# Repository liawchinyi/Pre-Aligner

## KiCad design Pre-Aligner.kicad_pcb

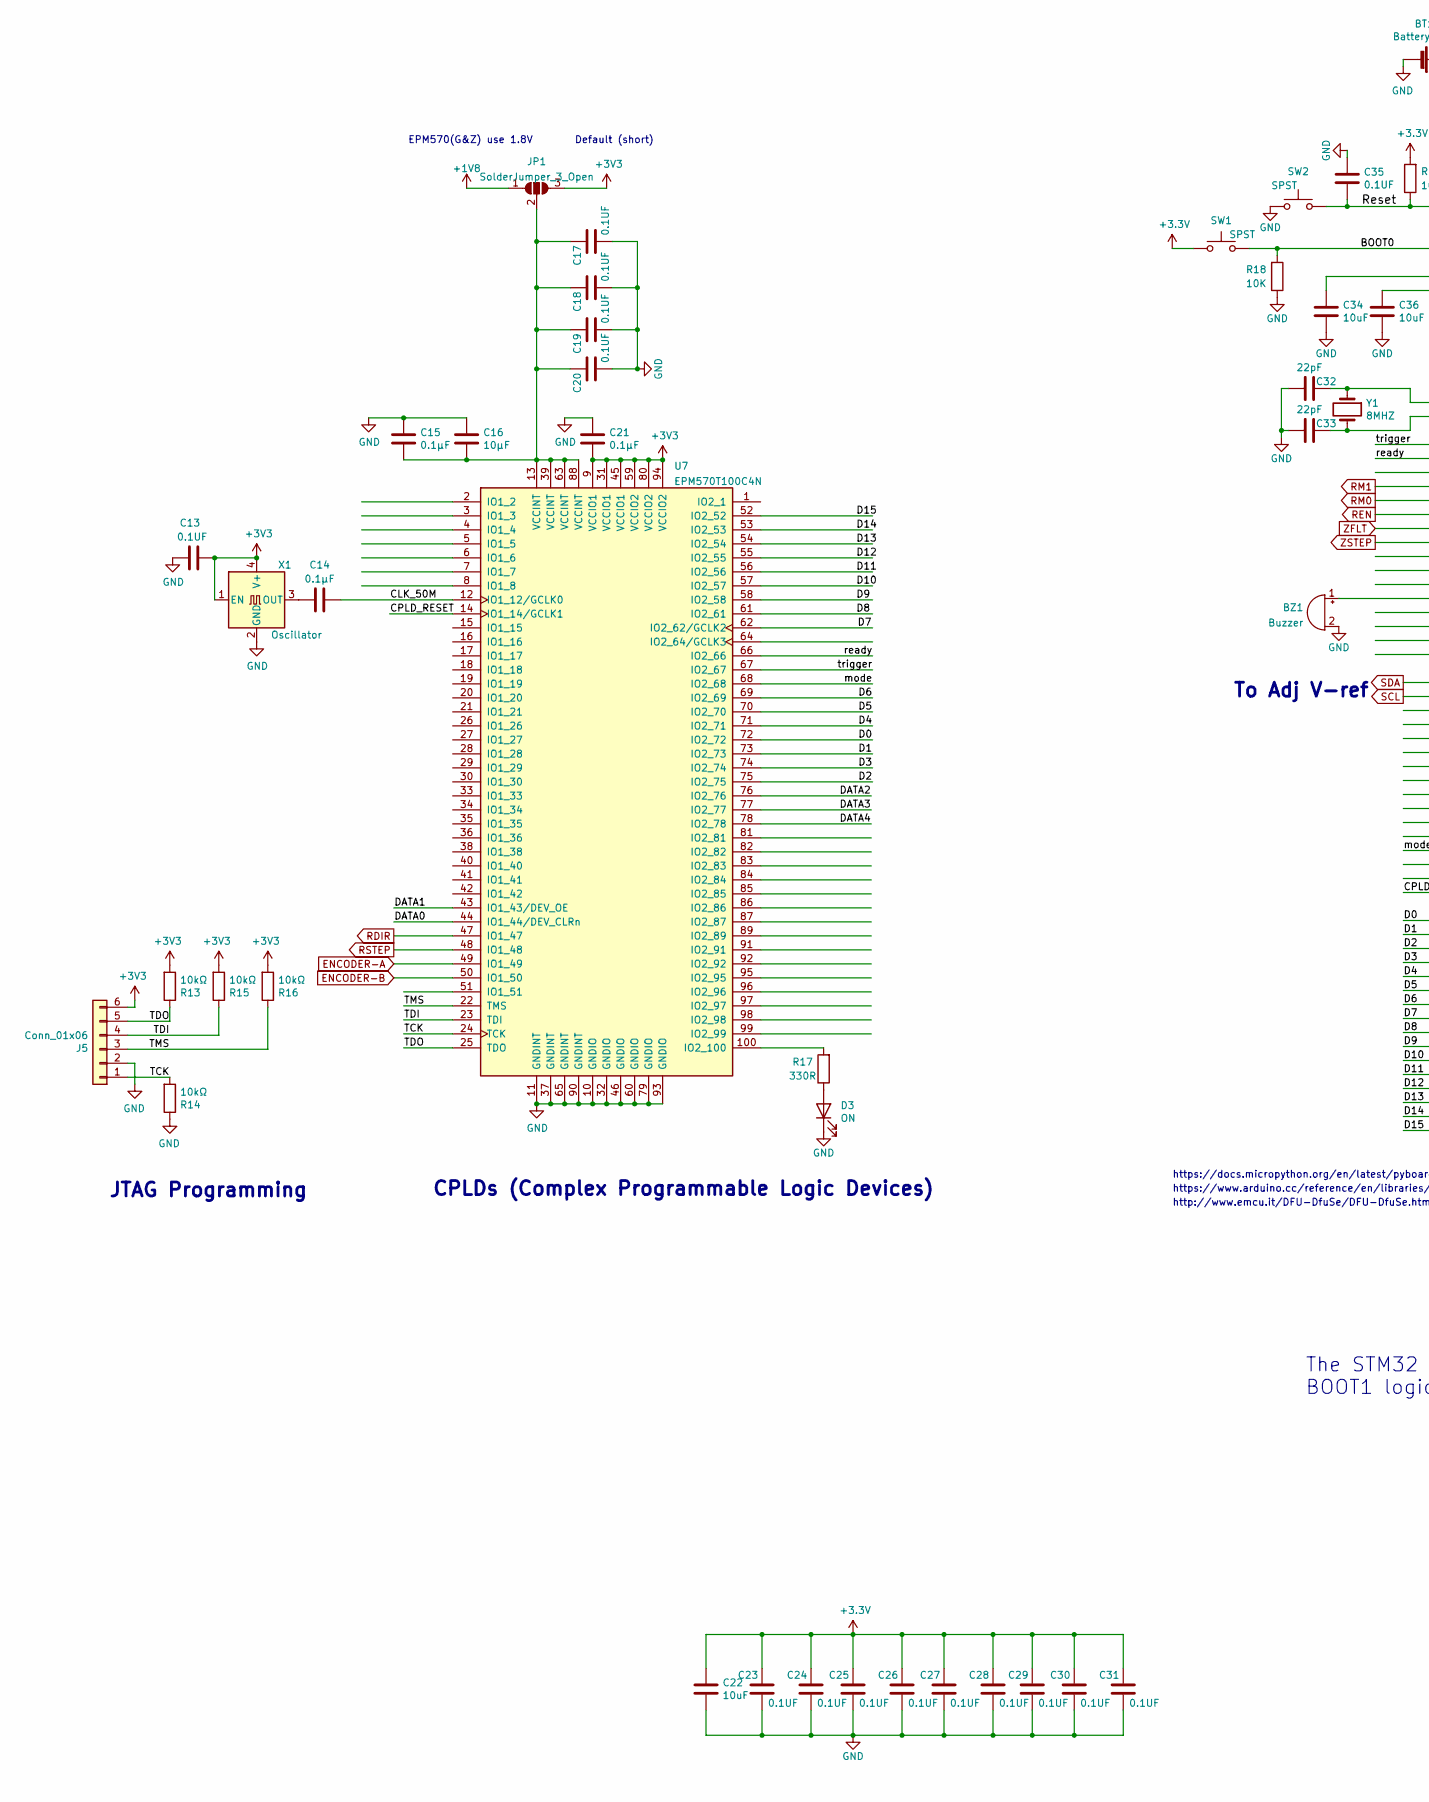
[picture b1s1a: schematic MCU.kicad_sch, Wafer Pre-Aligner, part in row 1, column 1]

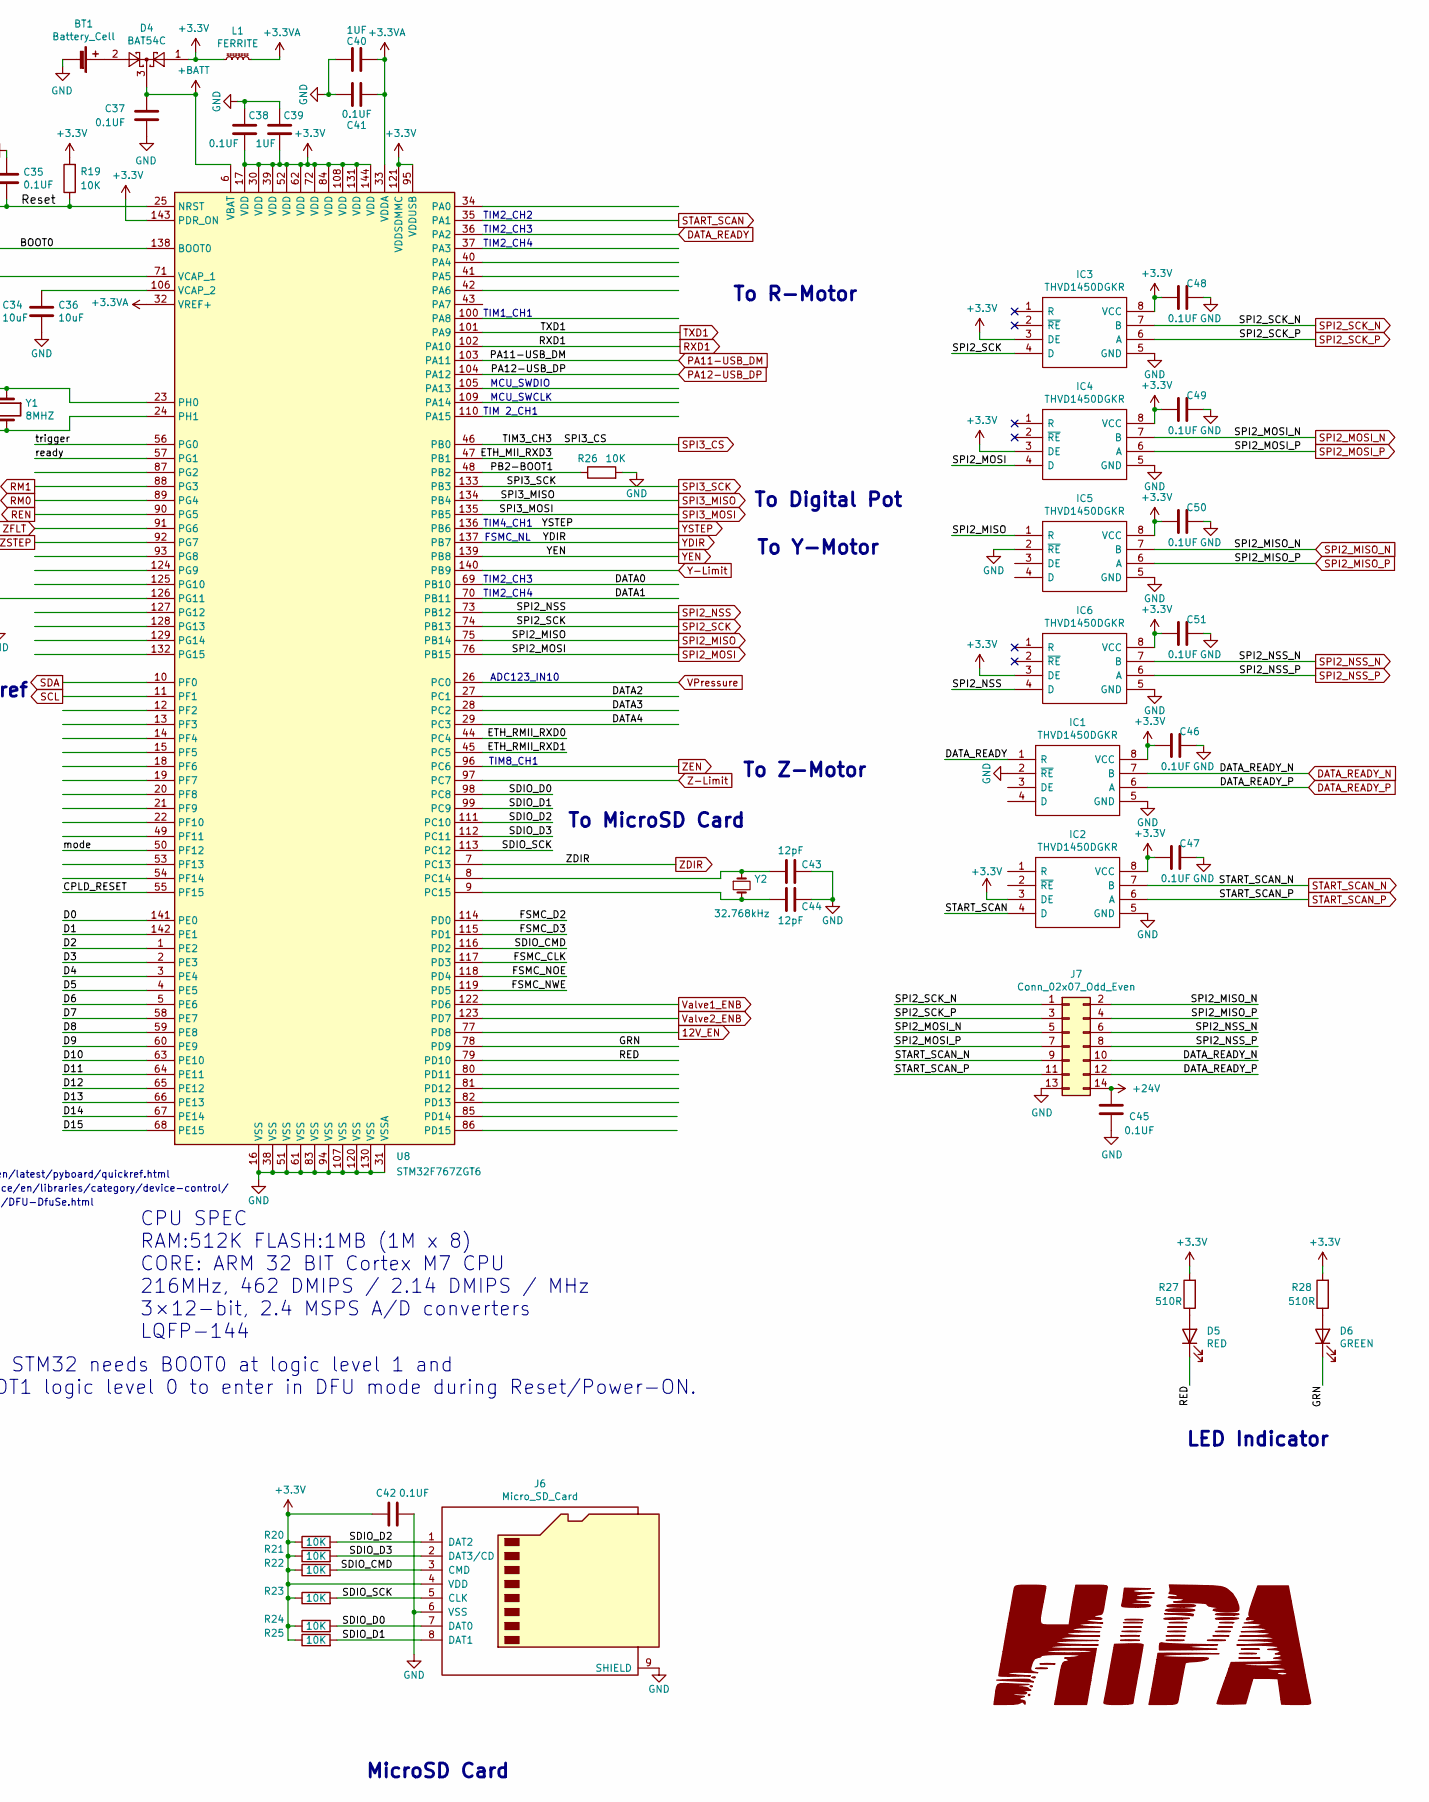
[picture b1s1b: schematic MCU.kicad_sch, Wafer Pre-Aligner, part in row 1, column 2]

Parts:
BT1: Battery_Cell; S8411-45R; Manufacturer_Part_Number S8411-45R
BZ1: Buzzer; MagneticBuzzer_PUI_AT-0927-TT-6-R; Manufacturer_Part_Number AT-0927-TT-6-R
C13, C17, C18, C19, C20, C23, C24, C25, C26, C27, C28, C29, C30, C31, C35, C37, C38, C41, C42, C45, C46, C47, C48, C49, C50, C51: 0.1UF; C_0603_1608Metric; Manufacturer_Part_Number C0603C104M5RACTU
C14: 0.1µF; C_0402_1005Metric; Manufacturer_Part_Number GRM155R71C104KA88J
C15, C21: 0.1µF; C_0603_1608Metric; Manufacturer_Part_Number CC0603KRX7R0BB104
C16: 10µF; C_1210_3225Metric; Manufacturer_Part_Number C1210C106K5RACTU
C22, C34, C36: 10uF; C_0603_1608Metric; Manufacturer_Part_Number GRM188D71A106KA73D
C32, C33: 22pF; C_0603_1608Metric; Manufacturer_Part_Number C0603C220J1GACTU
C39, C40: 1UF; C_0603_1608Metric; Manufacturer_Part_Number CL10B105MO8NNWC
C43, C44: 12pF; C_0402_1005Metric; Manufacturer_Part_Number 04025A120FAT2A
D3: ON; LED_0805_2012Metric; Manufacturer_Part_Number LTST-C171GKT
D4: BAT54C; SOT-23; Manufacturer_Part_Number BAT54C
D5: RED; LED_0805_2012Metric; Manufacturer_Part_Number LTST-C171KRKT
D6: GREEN; LED_0805_2012Metric; Manufacturer_Part_Number LTST-C171GKT
IC1, IC2, IC3, IC4, IC5, IC6: THVD1450DGKR; SOP65P490X110-8N; Manufacturer_Part_Number THVD1450DGKR; Mouser Part Number 595-THVD1450DGKR
J5: Conn_01x06; Molex_PicoBlade_53047-0610_1x06_P1.25mm_Vertical; Manufacturer_Part_Number 0530470610
J6: Micro_SD_Card; microSD_HC_Wuerth_693072010801; Manufacturer_Part_Number 693072010801
J7: Conn_02x07_Odd_Even; PinHeader_2x07_P2.54mm_Vertical; Manufacturer_Part_Number 5103308-2
JP1: SolderJumper_3_Open; SolderJumper-3_P1.3mm_Open_RoundedPad1.0x1.5mm_NumberLabels; Manufacturer_Part_Number Empty Do not mount
L1: FERRITE; L_0603_1608Metric; Manufacturer_Part_Number 742792651
R13, R14, R15, R16: 10kΩ; R_0603_1608Metric; Manufacturer_Part_Number RNCP0603FTD10K0
R17: 330R; R_0603_1608Metric; Manufacturer_Part_Number RC0603FR-07330RL
R18, R19, R20, R21, R22, R23, R24, R25, R26: 10K; R_0603_1608Metric; Manufacturer_Part_Number ERJ-3GEYJ103V
R27, R28: 510R; R_0603_1608Metric; Manufacturer_Part_Number RC0603JR-07510RL
SW1, SW2: SPST; SW_SPST_TL3342; Manufacturer_Part_Number TL3342F160QG/TR
U7: EPM570T100C4N; LQFP-100_14x14mm_P0.5mm; Manufacturer_Part_Number EPM570T100C4N
U8: STM32F767ZGT6; LQFP-144_20x20mm_P0.5mm; Manufacturer_Part_Number STM32F767ZGT6
X1: Oscillator; Oscillator_SMD_EuroQuartz_XO32-4Pin_3.2x2.5mm; Manufacturer_Part_Number ECS-2033-500-BN
Y1: 8MHZ; Crystal_SMD_Abracon_ABM7-2Pin_6.0x3.5mm; Manufacturer_Part_Number ABM7-8.000MHZ-D2Y-T
Y2: 32.768kHz; Crystal_SMD_2012-2Pin_2.0x1.2mm_HandSoldering; Manufacturer_Part_Number SC20S-12.5PF20PPM

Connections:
12V_EN: U8.77 (PD8); also elsewhere on the board
24V: C45.1, J7.14; also elsewhere on the board
+1V8: JP1.1 (A); also elsewhere on the board
+3.3VA: C40.2, C41.2, L1.2, U8.32 (VREF+), U8.33 (VDDA)
+BATT: C37.1, D4.3, U8.6 (VBAT)
/MCU/BOOT0: R18.2, SW1.2, U8.138 (BOOT0)
/MCU/CLK_50M: C14.2, U7.12 (IO1_12/GCLK0)
/MCU/CPLD_RESET: U7.14 (IO1_14/GCLK1), U8.55 (PF15)
/MCU/D0: U7.72 (IO2_72), U8.141 (PE0)
/MCU/D1: U7.73 (IO2_73), U8.142 (PE1)
/MCU/D2: U7.75 (IO2_75), U8.1 (PE2)
/MCU/D3: U7.74 (IO2_74), U8.2 (PE3)
/MCU/D4: U7.71 (IO2_71), U8.3 (PE4)
/MCU/D5: U7.70 (IO2_70), U8.4 (PE5)
/MCU/D6: U7.69 (IO2_69), U8.5 (PE6)
/MCU/D7: U7.62 (IO2_62/GCLK2), U8.58 (PE7)
/MCU/D8: U7.61 (IO2_61), U8.59 (PE8)
/MCU/D9: U7.58 (IO2_58), U8.60 (PE9)
/MCU/D10: U7.57 (IO2_57), U8.63 (PE10)
/MCU/D11: U7.56 (IO2_56), U8.64 (PE11)
/MCU/D12: U7.55 (IO2_55), U8.65 (PE12)
/MCU/D13: U7.54 (IO2_54), U8.66 (PE13)
/MCU/D14: U7.53 (IO2_53), U8.67 (PE14)
/MCU/D15: U7.52 (IO2_52), U8.68 (PE15)
/MCU/DATA0: U7.44 (IO1_44/DEV_CLRn), U8.69 (PB10)
/MCU/DATA1: U7.43 (IO1_43/DEV_OE), U8.70 (PB11)
/MCU/DATA2: U7.76 (IO2_76), U8.27 (PC1)
/MCU/DATA3: U7.77 (IO2_77), U8.28 (PC2)
/MCU/DATA4: U7.78 (IO2_78), U8.29 (PC3)
/MCU/ETH_MII_RXD3: U8.47 (PB1)
/MCU/ETH_RMII_RXD0: U8.44 (PC4)
/MCU/ETH_RMII_RXD1: U8.45 (PC5)
/MCU/FSMC_CLK: U8.117 (PD3)
/MCU/FSMC_D2: U8.114 (PD0)
/MCU/FSMC_D3: U8.115 (PD1)
/MCU/FSMC_NOE: U8.118 (PD4)
/MCU/FSMC_NWE: U8.119 (PD5)
/MCU/GRN: D6.1 (K), U8.78 (PD9)
/MCU/PB2-BOOT1: R26.1, U8.48 (PB2)
/MCU/RED: D5.1 (K), U8.79 (PD10)
/MCU/Reset: C35.1, R19.1, SW2.2, U8.25 (NRST)
/MCU/SDIO_CMD: J6.3 (CMD), R22.2, U8.116 (PD2)
/MCU/SDIO_D0: J6.7 (DAT0), R24.2, U8.98 (PC8)
/MCU/SDIO_D1: J6.8 (DAT1), R25.2, U8.99 (PC9)
/MCU/SDIO_D2: J6.1 (DAT2), R20.2, U8.111 (PC10)
/MCU/SDIO_D3: J6.2 (DAT3/CD), R21.2, U8.112 (PC11)
/MCU/SDIO_SCK: J6.5 (CLK), R23.2, U8.113 (PC12)
/MCU/TCK: J5.1, R14.2, U7.24 (TCK)
/MCU/TDI: J5.4, R15.1, U7.23 (TDI)
/MCU/TDO: J5.5, R13.1, U7.25 (TDO)
/MCU/TMS: J5.3, R16.1, U7.22 (TMS)
/MCU/mode: U7.68 (IO2_68), U8.50 (PF12)
/MCU/ready: U7.66 (IO2_66), U8.57 (PG1)
/MCU/trigger: U7.67 (IO2_67), U8.56 (PG0)
DATA_READY: IC1.1 (R), U8.36 (PA2)
DATA_READY_N: IC1.7 (B), J7.10
DATA_READY_P: IC1.6 (A), J7.12
ENCODER-A: U7.49 (IO1_49); also elsewhere on the board
ENCODER-B: U7.50 (IO1_50); also elsewhere on the board
GND: BT1.2 (-), BZ1.2 (+), C13.1, C15.1, C16.1, C17.1, C18.1, C19.1, C20.1, C21.1, C22.1, C23.1, C24.1, C25.1, C26.1, C27.1, C28.1, C29.1, C30.1, C31.1, C32.2, C33.2, C34.1, C35.2, C36.1, C37.2, C38.2, C39.2, C40.1, C41.1, C42.1, C43.1, C44.2, C45.2, C46.2, C47.2, C48.2, C49.2, C50.2, C51.2, D3.1 (K), IC1.2 (~RE), IC1.5 (GND), IC2.5 (GND), IC3.5 (GND), IC4.5 (GND), IC5.2 (~RE), IC5.5 (GND), IC6.5 (GND), J5.2, J6.6 (VSS), J6.9 (SHIELD), J7.13, R14.1, R18.1, R26.2, SW2.1, U7.10 (GNDIO), U7.11 (GNDINT), U7.32 (GNDIO), U7.37 (GNDINT), U7.46 (GNDIO), U7.60 (GNDIO), U7.65 (GNDINT), U7.79 (GNDIO), U7.90 (GNDINT), U7.93 (GNDIO), U8.16 (VSS), U8.31 (VSSA), U8.38 (VSS), U8.51 (VSS), U8.61 (VSS), U8.83 (VSS), U8.94 (VSS), U8.107 (VSS), U8.120 (VSS), U8.130 (VSS), X1.2 (GND); also elsewhere on the board
unnamed: BT1.1 (+), D4.2
unnamed: BZ1.1 (-), U8.126 (PG11)
unnamed: C14.1, X1.3 (OUT)
unnamed: C15.2, C16.2, C17.2, C18.2, C19.2, C20.2, JP1.2 (C), U7.13 (VCCINT), U7.39 (VCCINT), U7.63 (VCCINT), U7.88 (VCCINT)
unnamed: C32.1, U8.23 (PH0), Y1.1
unnamed: C33.1, U8.24 (PH1), Y1.2
unnamed: C34.2, U8.71 (VCAP_1)
unnamed: C36.2, U8.106 (VCAP_2)
unnamed: C43.2, U8.8 (PC14), Y2.1
unnamed: C44.1, U8.9 (PC15), Y2.2
unnamed: D3.2 (A), R17.1
unnamed: D5.2 (A), R27.1
unnamed: D6.2 (A), R28.1
unnamed: R17.2, U7.100 (IO2_100)
PA11-USB_DM: U8.103 (PA11); also elsewhere on the board
PA12-USB_DP: U8.104 (PA12); also elsewhere on the board
RDIR: U7.47 (IO1_47); also elsewhere on the board
REN: U8.90 (PG5); also elsewhere on the board
RM0: U8.89 (PG4); also elsewhere on the board
RM1: U8.88 (PG3); also elsewhere on the board
RSTEP: U7.48 (IO1_48); also elsewhere on the board
RXD1: U8.102 (PA10); also elsewhere on the board
SCL: U8.11 (PF1); also elsewhere on the board
SDA: U8.10 (PF0); also elsewhere on the board
SPI2_MISO: IC5.1 (R), U8.75 (PB14)
SPI2_MISO_N: IC5.7 (B), J7.2
SPI2_MISO_P: IC5.6 (A), J7.4
SPI2_MOSI: IC4.4 (D), U8.76 (PB15)
SPI2_MOSI_N: IC4.7 (B), J7.5
SPI2_MOSI_P: IC4.6 (A), J7.7
SPI2_NSS: IC6.4 (D), U8.73 (PB12)
SPI2_NSS_N: IC6.7 (B), J7.6
SPI2_NSS_P: IC6.6 (A), J7.8
SPI2_SCK: IC3.4 (D), U8.74 (PB13)
SPI2_SCK_N: IC3.7 (B), J7.1
SPI2_SCK_P: IC3.6 (A), J7.3
SPI3_CS: U8.46 (PB0); also elsewhere on the board
SPI3_MISO: U8.134 (PB4)
SPI3_MOSI: U8.135 (PB5); also elsewhere on the board
SPI3_SCK: U8.133 (PB3); also elsewhere on the board
START_SCAN: IC2.4 (D), U8.35 (PA1)
START_SCAN_N: IC2.7 (B), J7.9
START_SCAN_P: IC2.6 (A), J7.11
TXD1: U8.101 (PA9); also elsewhere on the board
VPressure: U8.26 (PC0); also elsewhere on the board
Valve1_ENB: U8.122 (PD6); also elsewhere on the board
Valve2_ENB: U8.123 (PD7); also elsewhere on the board
Y-Limit: U8.140 (PB9); also elsewhere on the board
YDIR: U8.137 (PB7); also elsewhere on the board
YEN: U8.139 (PB8); also elsewhere on the board
YSTEP: U8.136 (PB6); also elsewhere on the board
Z-Limit: U8.97 (PC7); also elsewhere on the board
ZDIR: U8.7 (PC13); also elsewhere on the board
ZEN: U8.96 (PC6); also elsewhere on the board
ZFLT: U8.91 (PG6); also elsewhere on the board
ZSTEP: U8.92 (PG7); also elsewhere on the board

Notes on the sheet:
TIM2_CH4
TIM4_CH1
TIM2_CH3
MicroSD Card
To Z-Motor
LED Indicator
TIM8_CH1
ADC123_IN10
http://www.emcu.it/DFU-DfuSe/DFU-DfuSe.html
To MicroSD Card
MCU_SWDIO
Default (short)
https://docs.micropython.org/en/latest/pyboard/quickref.html
TIM 2_CH1
TIM1_CH1
CPU SPEC RAM:512K FLASH:1MB (1M x 8) CORE: ARM 32 BIT Cortex M7 CPU 216MHz, 462 DMIPS / 2.14 DMIPS / MHz 3×12-bit, 2.4 MSPS A/D converters LQFP-144
CPLDs (Complex Programmable Logic Devices)
MCU_SWCLK
https://www.arduino.cc/reference/en/libraries/category/device-control/
To Y-Motor
TIM2_CH2
JTAG Programming
FSMC_NL
To Adj V-ref
To R-Motor
The STM32 needs BOOT0 at logic level 1 and BOOT1 logic level 0 to enter in DFU mode during Reset/Power-ON.
To Digital Pot
EPM570(G&Z) use 1.8V

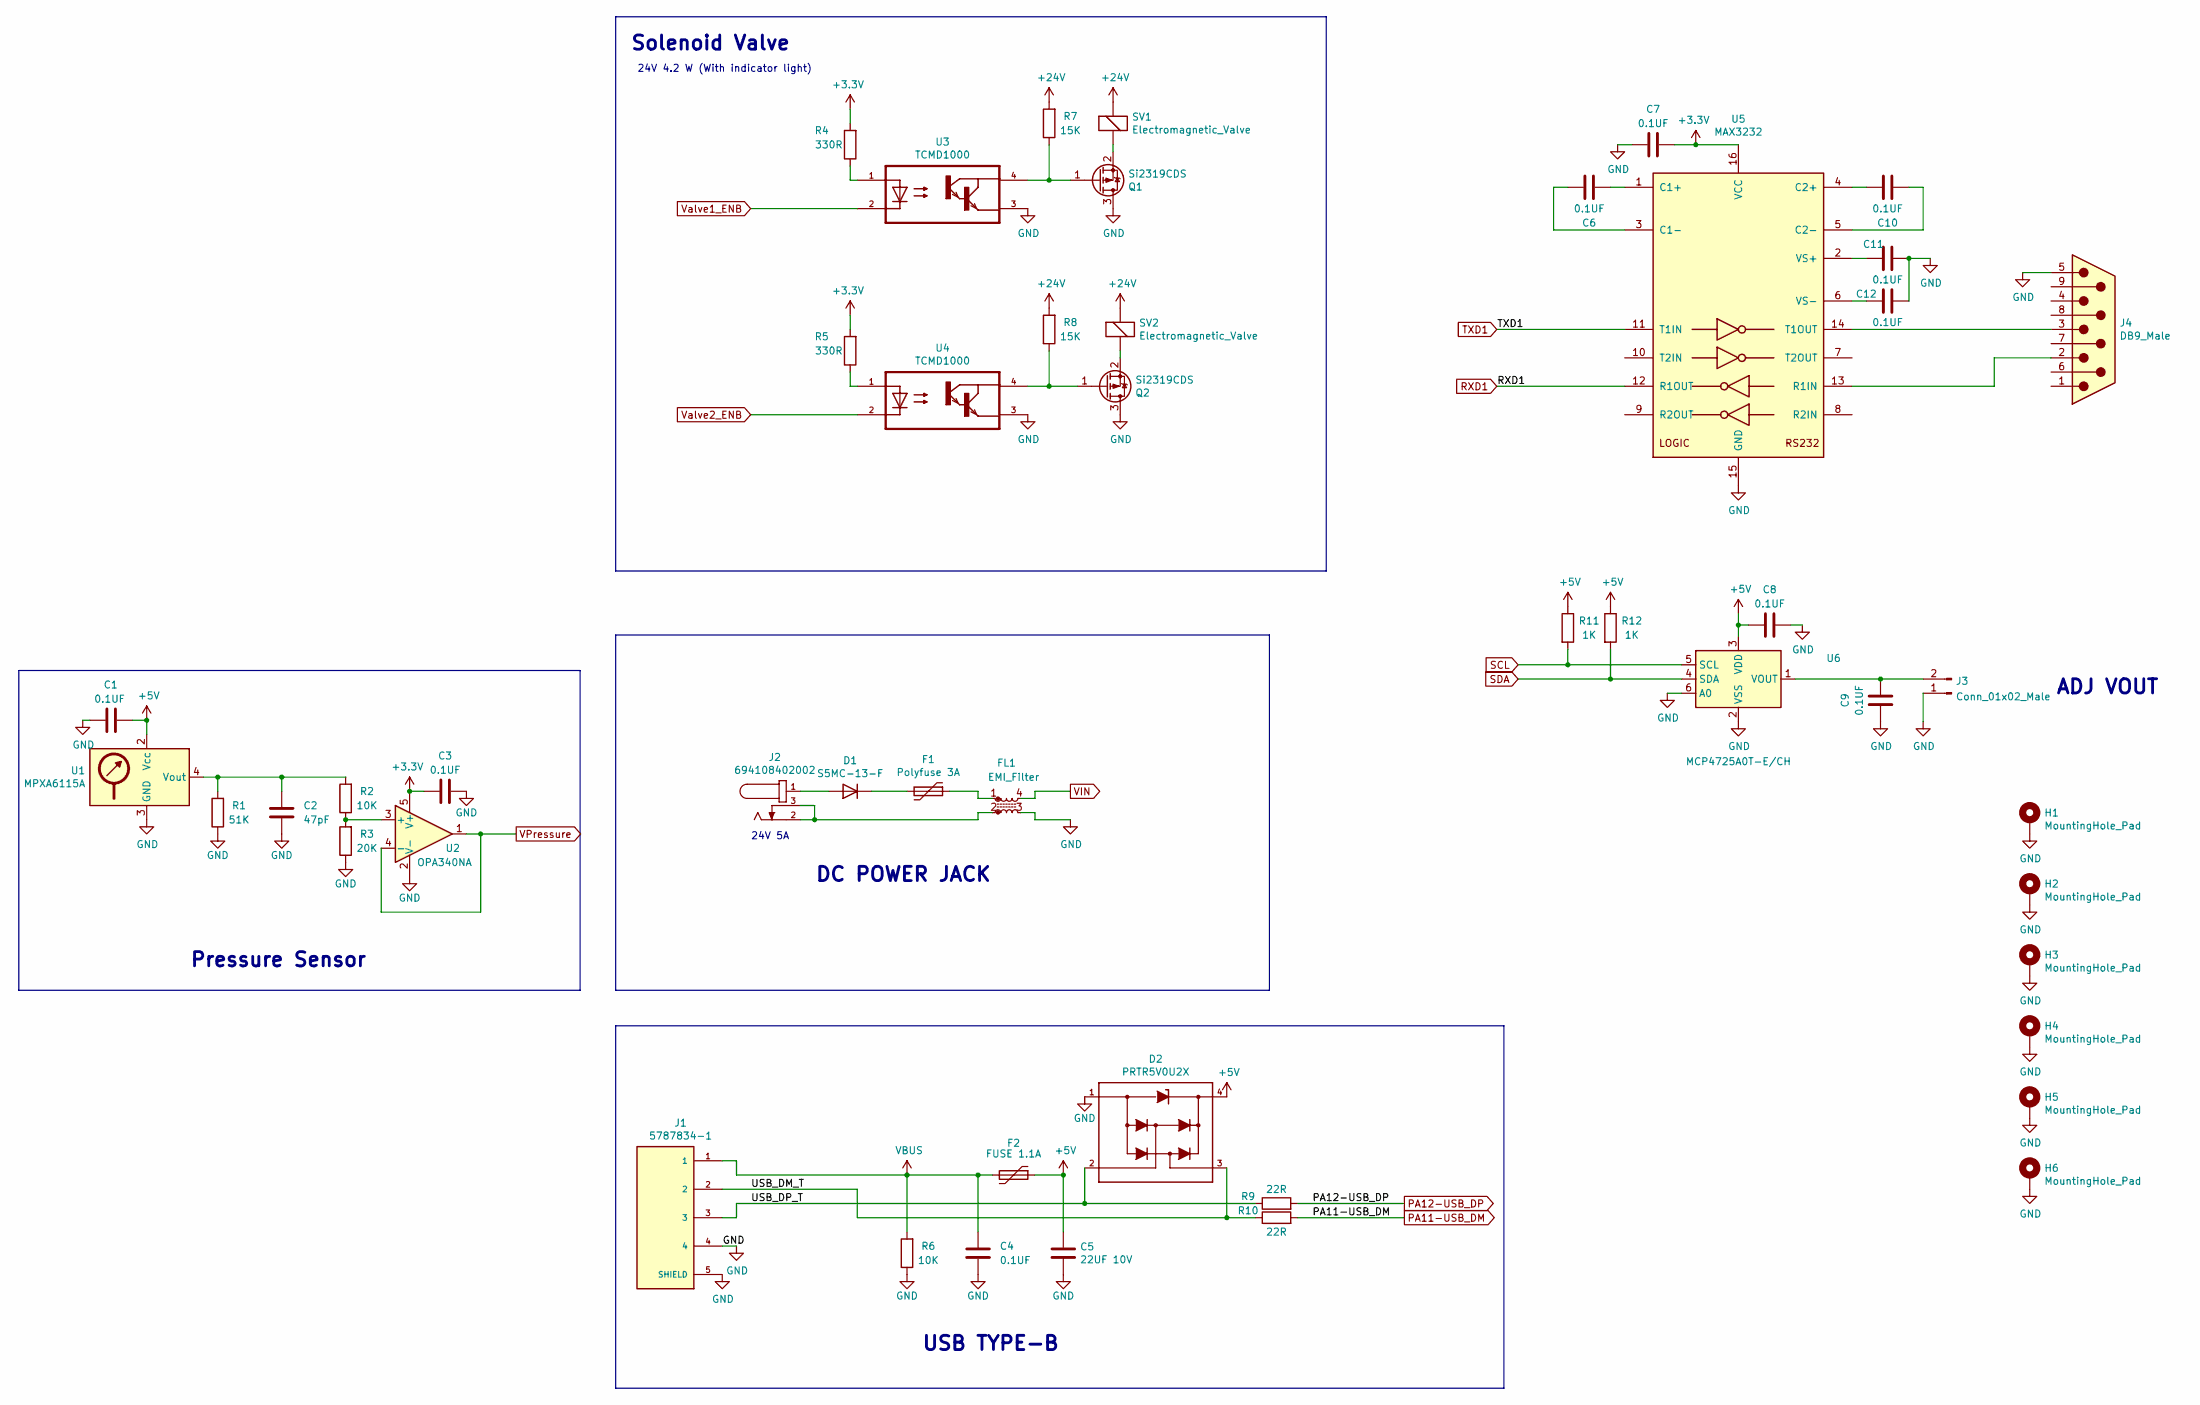
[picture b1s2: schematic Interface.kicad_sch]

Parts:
C1, C3, C4, C6, C7, C8, C9, C10, C11, C12: 0.1UF; C_0603_1608Metric; Manufacturer_Part_Number C0603C104M5RACTU
C2: 47pF; C_0603_1608Metric; Manufacturer_Part_Number 251R14S470GV4T
C5: 22UF 10V; C_0805_2012Metric; Manufacturer_Part_Number GRM21BR61A226ME51L
D1: S5MC-13-F; Manufacturer_Part_Number S5MC-13-F
D2: PRTR5V0U2X; SOT190P230X110-4N; Manufacturer_Part_Number PRTR5V0U2X,215
F1: Polyfuse 3A; Fuse_Bourns_MF-RHT1300; Manufacturer_Part_Number MF-RX300/72-2
F2: FUSE 1.1A; Fuse_1812_4532Metric_Pad1.30x3.40mm_HandSolder; Manufacturer_Part_Number 1812L110/33MR
FL1: EMI_Filter; ACM7060-701-2PL-TL; Manufacturer_Part_Number ACM7060-701-2PL-TL01
H1, H2, H3, H4, H5, H6: MountingHole_Pad; MountingHole_3.5mm_Pad; Manufacturer_Part_Number Empty Do not mount
J1: 5787834-1; USB_B_TE_5787834_Vertical; Manufacturer_Part_Number 5787834-1
J2: 694108402002; Manufacturer_Part_Number 694108402002
J3: Conn_01x02_Male; Molex_KK-254_AE-6410-02A_1x02_P2.54mm_Vertical; Manufacturer_Part_Number 0022272021
J4: DB9_Male; DSUB-9_Male_Vertical_P2.77x2.84mm_MountingHoles; Manufacturer_Part_Number 5747871-8
Q1, Q2: Si2319CDS; SOT-23; Manufacturer_Part_Number SI2319CDS-T1-BE3
R1: 51K; R_0603_1608Metric; Manufacturer_Part_Number RR0816P-513-D
R2, R6: 10K; R_0603_1608Metric; Manufacturer_Part_Number ERJ-3GEYJ103V
R3: 20K; R_0603_1608Metric; Manufacturer_Part_Number ERA-3AEB203V
R4, R5: 330R; R_0603_1608Metric; Manufacturer_Part_Number RC0603JR-07330RL
R7, R8: 15K; R_0603_1608Metric; Manufacturer_Part_Number ERA-3AEB153V
R9, R10: 22R; R_0603_1608Metric; Manufacturer_Part_Number RC0603FR-0722RL
R11, R12: 1K; R_0603_1608Metric; Manufacturer_Part_Number RC0603JR-071KL
SV1, SV2: Electromagnetic_Valve; Molex_KK-254_AE-6410-02A_1x02_P2.54mm_Vertical; Manufacturer_Part_Number 0022272021
U1: MPXA6115A; SOP254P1821X584-8N; Manufacturer_Part_Number MPXA6115AC6U
U2: OPA340NA; SOT-23-5; Manufacturer_Part_Number OPA340NA/3K
U3, U4: TCMD1000; SOP127P695X210-4N; Manufacturer_Part_Number TCMD1000
U5: MAX3232; SOIC-16_3.9x9.9mm_P1.27mm; Manufacturer_Part_Number MAX3232ESE+T
U6: MCP4725A0T-E/CH; SOT-23-6; Manufacturer_Part_Number MCP4725A0T-E/CH

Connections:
24V: R7.2, R8.2, SV1.1 (-), SV2.1 (-); also elsewhere on the board
+5V: C1.2, C5.1, C8.2, D2.4, F2.1, R11.1, R12.1, U1.2 (Vcc), U6.3 (VDD); also elsewhere on the board
/Interface/USB_DM_T: D2.3, J1.2, R10.1
/Interface/USB_DP_T: D2.2, J1.3, R9.1
GND: C1.1, C2.2, C3.1, C4.2, C5.2, C7.2, C8.1, C9.2, C11.2, C12.2, D2.1, FL1.3, H1.1, H2.1, H3.1, H4.1, H5.1, H6.1, J1.4, J1.5 (SHIELD), J3.1, J4.5, Q1.3 (D), Q2.3 (D), R1.1, R3.1, R6.1, U1.3 (GND), U2.2 (V-), U3.3, U4.3, U5.15 (GND), U6.2 (VSS), U6.6 (A0); also elsewhere on the board
unnamed: C2.1, R1.2, R2.2, U1.4 (Vout)
unnamed: C6.1, U5.3 (C1-)
unnamed: C6.2, U5.1 (C1+)
unnamed: C9.1, J3.2, U6.1 (VOUT)
unnamed: C10.1, U5.4 (C2+)
unnamed: C10.2, U5.5 (C2-)
unnamed: C11.1, U5.2 (VS+)
unnamed: C12.1, U5.6 (VS-)
unnamed: D1.1 (K), F1.2
unnamed: D1.2 (A), J2.1
unnamed: F1.1, FL1.1
unnamed: FL1.2, J2.2, J2.3
unnamed: J4.2, U5.13 (R1IN)
unnamed: J4.3, U5.14 (T1OUT)
unnamed: Q1.1 (G), R7.1, U3.4
unnamed: Q1.2 (S), SV1.2 (+)
unnamed: Q2.1 (G), R8.1, U4.4
unnamed: Q2.2 (S), SV2.2 (+)
unnamed: R2.1, R3.2, U2.3 (+)
unnamed: R4.1, U3.1
unnamed: R5.1, U4.1
PA11-USB_DM: R10.2; also elsewhere on the board
PA12-USB_DP: R9.2; also elsewhere on the board
RXD1: U5.12 (R1OUT); also elsewhere on the board
SCL: R11.2, U6.5 (SCL); also elsewhere on the board
SDA: R12.2, U6.4 (SDA); also elsewhere on the board
TXD1: U5.11 (T1IN); also elsewhere on the board
VBUS: C4.1, F2.2, J1.1, R6.2
VIN: FL1.4; also elsewhere on the board
VPressure: U2.1, U2.4 (-); also elsewhere on the board
Valve1_ENB: U3.2; also elsewhere on the board
Valve2_ENB: U4.2; also elsewhere on the board

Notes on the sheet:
USB TYPE-B
ADJ VOUT
24V 4.2 W (With indicator light)
Pressure Sensor
24V 5A
Solenoid Valve
DC POWER JACK

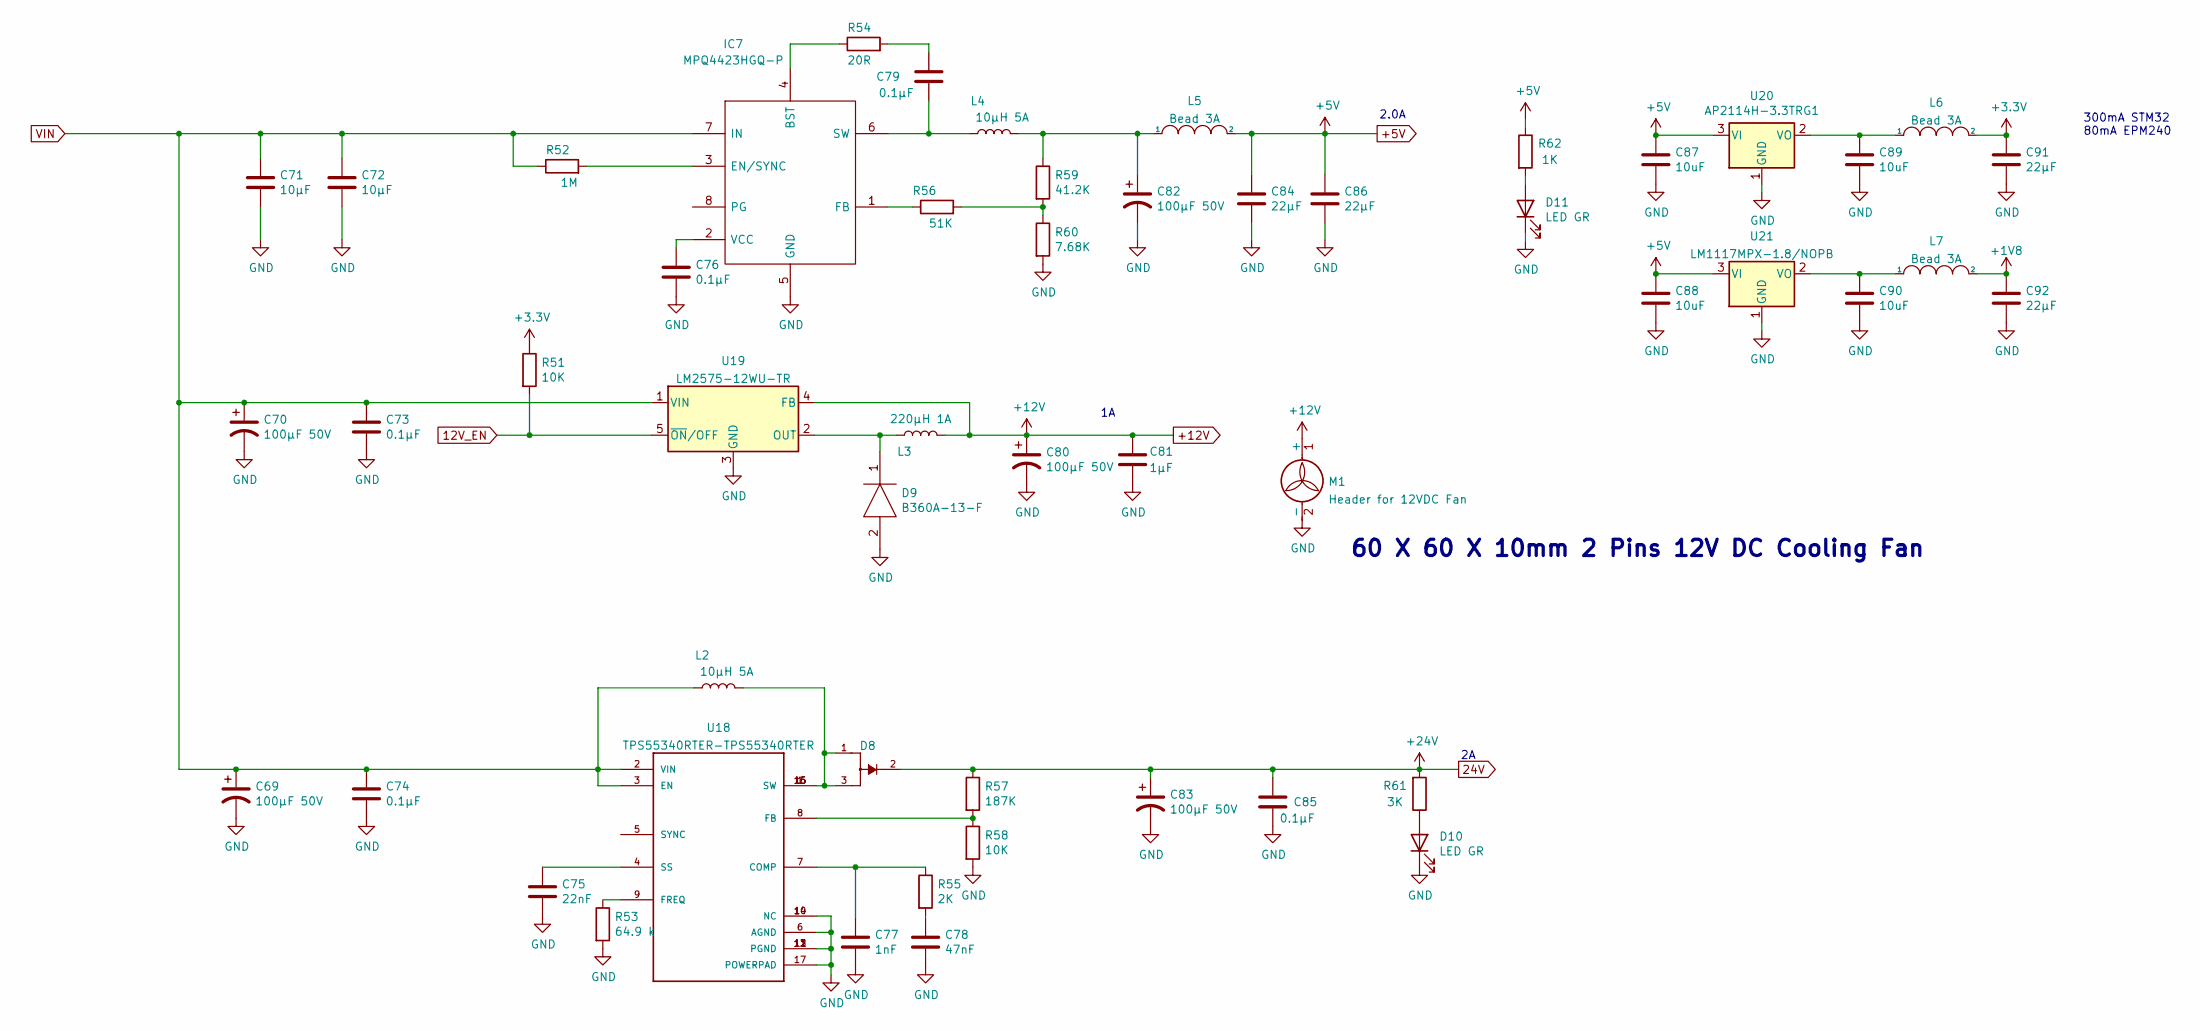
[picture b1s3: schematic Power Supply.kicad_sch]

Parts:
C69, C70, C80, C82, C83: 100µF 50V; CP_Elec_10x10; Manufacturer_Part_Number EEE-FC1H101P
C71, C72: 10µF; C_1210_3225Metric; Manufacturer_Part_Number C1210C106K5RACTU
C73, C74, C76, C79: 0.1µF; C_0603_1608Metric; Manufacturer_Part_Number CC0603KRX7R0BB104
C75: 22nF; C_0603_1608Metric; Manufacturer_Part_Number MC0603B223K500CT
C77: 1nF; C_0603_1608Metric; Manufacturer_Part_Number CC0603KRX7R9BB102
C78: 47nF; C_0603_1608Metric; Manufacturer_Part_Number MC0603B473K500CT
C81: 1µF; C_0603_1608Metric; Manufacturer_Part_Number Samsung Electro-Mechanics
C84, C86, C91, C92: 22µF; C_1210_3225Metric; Manufacturer_Part_Number CGA6P1X7R1C226M250AC
C85: 0.1µF; C_0402_1005Metric; Manufacturer_Part_Number GRM155R71C104KA88J
C87, C88, C89, C90: 10uF; C_0603_1608Metric; Manufacturer_Part_Number GRM188D71A106KA73D
D8: SBRD10200TR; ATPAK-2; Manufacturer_Part_Number SBRD10200
D9: B360A-13-F; DIOM5226X240N; Manufacturer_Part_Number B360A-13-F; Mouser Part Number 621-B360A-F
D10: LED GR; LED_D5.0mm; Manufacturer_Part_Number LTL-307GLC
D11: LED GR; LED_0805_2012Metric; Manufacturer_Part_Number LTST-C171GKT
IC7: MPQ4423HGQ-P; SON65P300X300X100-8N-D; Manufacturer_Part_Number MPQ4423HGQ-P; Mouser Part Number 946-MPQ4423HGQ-P
L2, L4: 10µH 5A; L_12x12mm_H6mm; Manufacturer_Part_Number 74477110
L3: 220µH 1A; L_Wuerth_HCM-7070; Manufacturer_Part_Number 74404084221
L5, L6, L7: Bead 3A; L_1210_3225Metric; Manufacturer_Part_Number FBMH3225HM601NT
M1: Header for 12VDC Fan; Molex_KK-254_AE-6410-02A_1x02_P2.54mm_Vertical; Manufacturer_Part_Number 0022272021
R51: 10K; R_0603_1608Metric; Manufacturer_Part_Number RT0603DRD0710KL
R52: 1M; R_0603_1608Metric; Manufacturer_Part_Number HVCB0603FDC1M00
R53: 64.9 k; R_0603_1608Metric; Manufacturer_Part_Number RC0603FR-0764K9L
R54: 20R; R_0603_1608Metric; Manufacturer_Part_Number RC0603FR-0720RL
R55: 2K; R_0603_1608Metric; Manufacturer_Part_Number RNCP0603FTD2K00
R56: 51K; R_0603_1608Metric; Manufacturer_Part_Number RT0603FRE0751KL
R57: 187K; R_0603_1608Metric; Manufacturer_Part_Number RMCF0603FT187K
R58: 10K; R_0603_1608Metric; Manufacturer_Part_Number RNCF0603TKY10K0
R59: 41.2K; R_0603_1608Metric; Manufacturer_Part_Number RMCF0603FT41K2
R60: 7.68K; R_0603_1608Metric; Manufacturer_Part_Number RT0603BRE077K68L
R61: 3K; R_0805_2012Metric; Manufacturer_Part_Number ERA-6AEB302V
R62: 1K; R_0603_1608Metric; Manufacturer_Part_Number RC0603JR-071KL
U18: TPS55340RTER-TPS55340RTER; QFN50P300X300X100-17N; Manufacturer_Part_Number TPS55340RTER
U19: LM2575-12WU-TR; TO-263-5_TabPin3; Manufacturer_Part_Number LM2575-12WU-TR
U20: AP2114H-3.3TRG1; SOT-223-3_TabPin2; Manufacturer_Part_Number AP2114H-3.3TRG1
U21: LM1117MPX-1.8/NOPB; SOT-223-3_TabPin2; Manufacturer_Part_Number LM1117MPX-1.8/NOPB

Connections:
12V_EN: R51.2, U19.5 (~ON/OFF); also elsewhere on the board
24V: C83.1, C85.1, D8.2, R57.1, R61.2; also elsewhere on the board
+1V8: C92.1, L7.2; also elsewhere on the board
+5V: C84.1, C86.1, C87.2, C88.2, L5.2, R62.1, U20.3 (VI), U21.3 (VI); also elsewhere on the board
+12V: C80.1, C81.2, L3.2, M1.1 (+), U19.4 (FB)
GND: C69.2, C70.2, C71.2, C72.2, C73.2, C74.2, C75.2, C76.2, C77.2, C78.2, C80.2, C81.1, C82.2, C83.2, C84.2, C85.2, C86.2, C87.1, C88.1, C89.1, C90.1, C91.2, C92.2, D9.2, D10.1 (K), D11.1 (K), IC7.5 (GND), M1.2 (-), R53.2, R58.2, R60.2, U18.6 (AGND), U18.10 (NC), U18.11 (PGND), U18.12 (PGND), U18.13 (PGND), U18.14 (NC), U18.17 (POWERPAD), U19.3 (GND), U20.1 (GND), U21.1 (GND); also elsewhere on the board
unnamed: C75.1, U18.4 (SS)
unnamed: C76.1, IC7.2 (VCC)
unnamed: C77.1, R55.1, U18.7 (COMP)
unnamed: C78.1, R55.2
unnamed: C79.1, R54.2
unnamed: C79.2, IC7.6 (SW), L4.1
unnamed: C82.1, L4.2, L5.1, R59.1
unnamed: C89.2, L6.1, U20.2 (VO)
unnamed: C90.2, L7.1, U21.2 (VO)
unnamed: D8.1, D8.3, L2.2, U18.1 (SW), U18.15 (SW), U18.16 (SW)
unnamed: D9.1, L3.1, U19.2 (OUT)
unnamed: D10.2 (A), R61.1
unnamed: D11.2 (A), R62.2
unnamed: IC7.1 (FB), R56.1
unnamed: IC7.3 (EN/SYNC), R52.2
unnamed: IC7.4 (BST), R54.1
unnamed: R53.1, U18.9 (FREQ)
unnamed: R56.2, R59.2, R60.1
unnamed: R57.2, R58.1, U18.8 (FB)
VIN: C69.1, C70.1, C71.1, C72.1, C73.1, C74.1, IC7.7 (IN), L2.1, R52.1, U18.2 (VIN), U18.3 (EN), U19.1 (VIN); also elsewhere on the board

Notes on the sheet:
2.0A
300mA STM32 80mA EPM240
60 X 60 X 10mm 2 Pins 12V DC Cooling Fan

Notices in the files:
parts and their libraries:
Copyright 2016 Accelerated Designs. All rights reserved.
Copyright 2021 Accelerated Designs. All rights reserved.
